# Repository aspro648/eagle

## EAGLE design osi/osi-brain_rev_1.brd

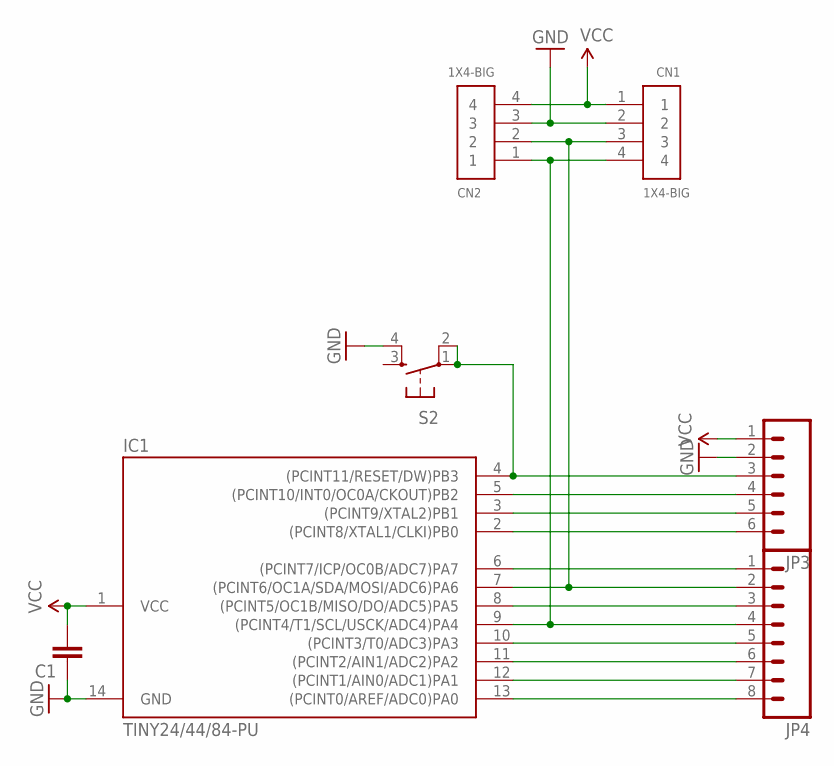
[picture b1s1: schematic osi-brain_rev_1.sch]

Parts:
C1: CAPKIT; CAP-PTH-SMALL-KIT
CN1, CN2: 1X4-BIG; 1X04-BIG
IC1: TINY24/44/84-PU; DIL14
JP3: M06SIP; 1X06
JP4: M081X08; 1X08
S2: TAC_SWITCHPTH; TACTILE-PTH

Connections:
D0: IC1.13 ((PCINT0/AREF/ADC0)PA0), JP4.8
D1: IC1.12 ((PCINT1/AIN0/ADC1)PA1), JP4.7
D2: IC1.11 ((PCINT2/AIN1/ADC2)PA2), JP4.6
D3: IC1.10 ((PCINT3/T0/ADC3)PA3), JP4.5
D4: CN1.4, CN2.1, IC1.9 ((PCINT4/T1/SCL/USCK/ADC4)PA4), JP4.4
D5: IC1.8 ((PCINT5/OC1B/MISO/DO/ADC5)PA5), JP4.3
D6: CN1.3, CN2.2, IC1.7 ((PCINT6/OC1A/SDA/MOSI/ADC6)PA6), JP4.2
D7: IC1.6 ((PCINT7/ICP/OC0B/ADC7)PA7), JP4.1
D8: IC1.5 ((PCINT10/INT0/OC0A/CKOUT)PB2), JP3.4
D9: IC1.3 ((PCINT9/XTAL2)PB1), JP3.5
D10: IC1.2 ((PCINT8/XTAL1/CLKI)PB0), JP3.6
GND: C1.1, CN1.2, CN2.3, IC1.14 (GND), JP3.2, S2.4
RESET: IC1.4 ((PCINT11/RESET/DW)PB3), JP3.3, S2.1, S2.2
VCC: C1.2, CN1.1, CN2.4, IC1.1 (VCC), JP3.1

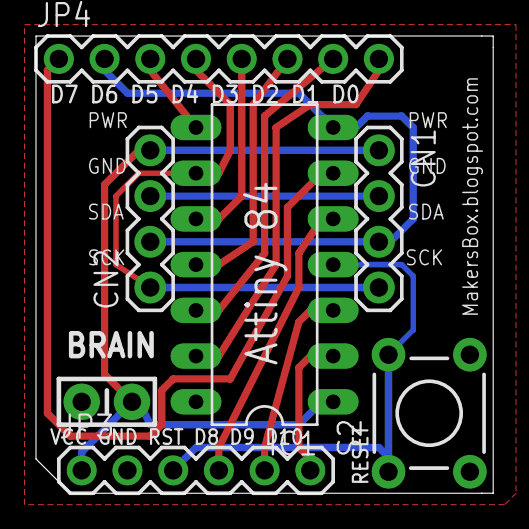
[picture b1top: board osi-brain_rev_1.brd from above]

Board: 2 copper layers, 25.4 x 25.4 mm, 7 parts (0 on the bottom side), 14 nets.

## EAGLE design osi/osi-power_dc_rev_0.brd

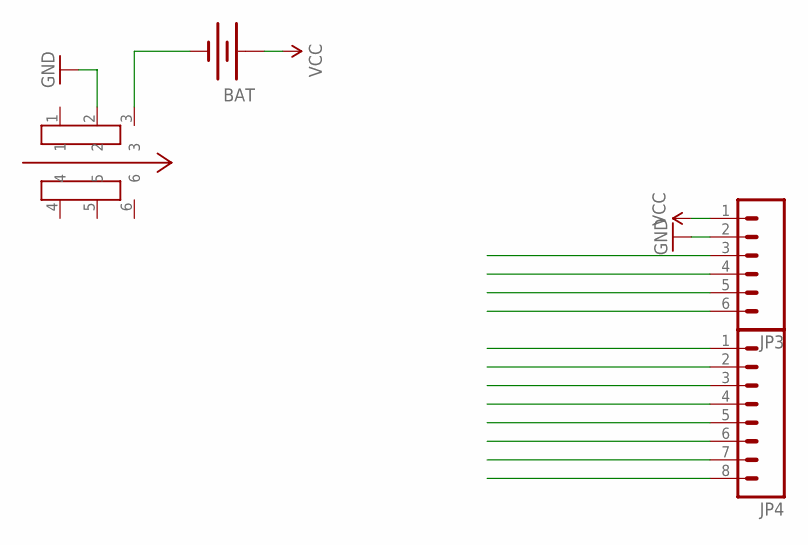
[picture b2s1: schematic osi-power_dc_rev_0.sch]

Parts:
BAT: BATTERY20PTH; BATTCOM_20MM_PTH
JP3: M06SIP; 1X06
JP4: M081X08; 1X08
U$1: SWITCH

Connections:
D0: JP4.8
D1: JP4.7
D2: JP4.6
D3: JP4.5
D4: JP4.4
D5: JP4.3
D6: JP4.2
D7: JP4.1
D8: JP3.4
D9: JP3.5
D10: JP3.6
GND: JP3.2, U$1.2
unnamed: BAT.2 (-), U$1.3
RESET: JP3.3
VCC: BAT.1 (+), JP3.1

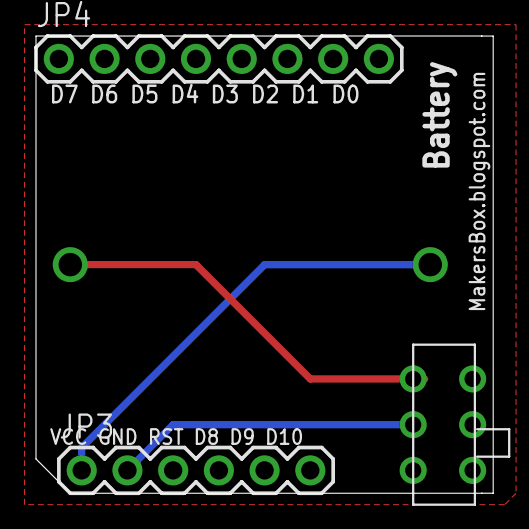
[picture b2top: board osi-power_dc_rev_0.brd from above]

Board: 2 copper layers, 25.4 x 25.4 mm, 4 parts (0 on the bottom side), 3 nets.

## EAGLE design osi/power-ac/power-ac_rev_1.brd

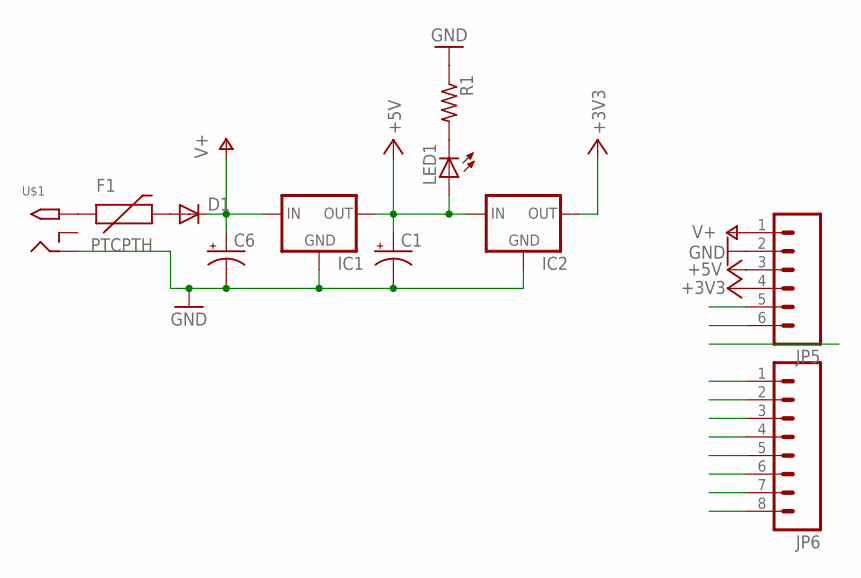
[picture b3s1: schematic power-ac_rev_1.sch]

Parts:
C1, C6: CAP_POLPTH1; CPOL-RADIAL-100UF-25V
D1: DIODE1N4148; DIODE-1N4148
F1: PTCPTH; PTC
IC1: V_REG_78XX-TO-220; TO-220-ALT
IC2: MCP1700INLINE; TO92-INLINE
JP5: M06SIP; 1X06
JP6: M081X08; 1X08
LED1: LED3MM
R1: R-US_0204/2V; 0204V
U$1: 2.1MMJACKTHM; PJ-102A

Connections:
+3V3: IC2.3 (OUT), JP5.4
+5V: C1.1 (+), IC1.OUT, IC2.2 (IN), JP5.3, LED1.A
AREF_D0: JP6.8
D1: JP6.7
D2: JP6.6
D3: JP6.5
D5: JP6.3
D7: JP6.1
D8: JP5.5
D9: JP5.6
GND: C1.2 (-), C6.2 (-), IC1.GND, IC2.1 (GND), JP5.2, R1.1, U$1.RING
unnamed: F1.P$1 (1), U$1.TIP
unnamed: LED1.K (C), R1.2
unnamed: D1.A, F1.P$2 (2)
SCL_D4: JP6.4
SDA_D6: JP6.2
V+: C6.1 (+), D1.C, IC1.IN, JP5.1

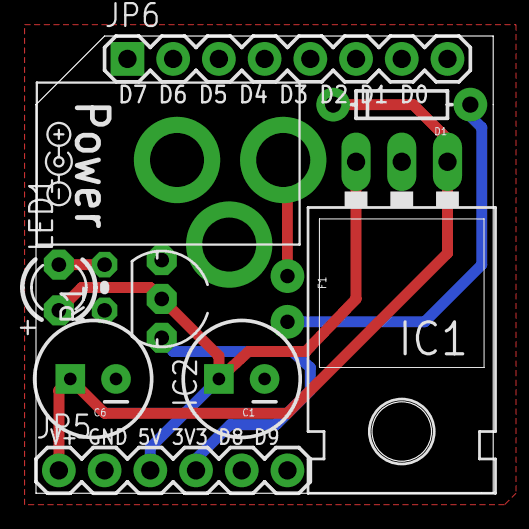
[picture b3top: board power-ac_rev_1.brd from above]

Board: 2 copper layers, 25.4 x 25.4 mm, 13 parts (0 on the bottom side), 7 nets.

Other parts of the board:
U$2: DC_POS_CTR
U$3: DC_POS_CTR-BOTTOM

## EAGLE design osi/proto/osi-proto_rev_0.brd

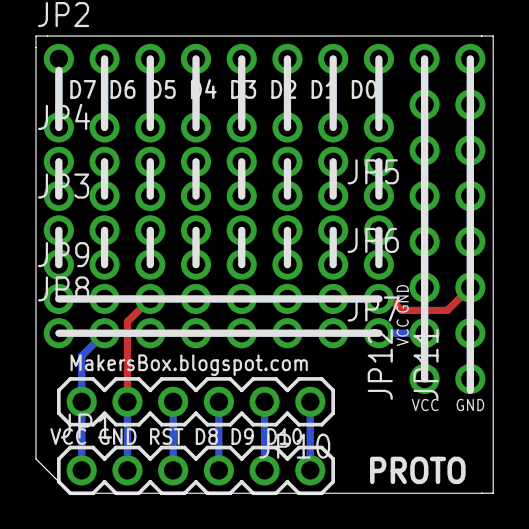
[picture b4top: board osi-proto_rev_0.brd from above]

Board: 2 copper layers, 25.4 x 25.4 mm, 12 parts (0 on the bottom side), 30 nets.

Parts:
JP1, JP10: 1X06
JP2, JP3, JP4, JP5, JP6, JP7, JP8, JP9, JP11, JP12: 1X08

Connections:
D0: JP2.8, JP5.1
D1: JP2.7, JP5.2
D2: JP2.6, JP5.3
D3: JP2.5, JP5.4
D5: JP2.3, JP5.6
D7: JP2.1, JP5.8
GND: JP1.2, JP9.1, JP9.2, JP9.3, JP9.4, JP9.5, JP9.6, JP9.7, JP9.8, JP10.5, JP11.1, JP11.2, JP11.3, JP11.4, JP11.5, JP11.6, JP11.7, JP11.8
unnamed: JP4.8, JP6.1
unnamed: JP4.7, JP6.2
unnamed: JP4.6, JP6.3
unnamed: JP4.5, JP6.4
unnamed: JP4.4, JP6.5
unnamed: JP4.3, JP6.6
unnamed: JP4.2, JP6.7
unnamed: JP4.1, JP6.8
unnamed: JP3.1, JP7.8
unnamed: JP3.2, JP7.7
unnamed: JP3.3, JP7.6
unnamed: JP3.4, JP7.5
unnamed: JP3.5, JP7.4
unnamed: JP3.6, JP7.3
unnamed: JP3.7, JP7.2
unnamed: JP3.8, JP7.1
unnamed: JP1.6, JP10.1
unnamed: JP1.5, JP10.2
unnamed: JP1.4, JP10.3
unnamed: JP1.3, JP10.4
SCK: JP2.2, JP5.7
SDA: JP2.4, JP5.5
VCC: JP1.1, JP8.1, JP8.2, JP8.3, JP8.4, JP8.5, JP8.6, JP8.7, JP8.8, JP10.6, JP12.1, JP12.2, JP12.3, JP12.4, JP12.5, JP12.6, JP12.7, JP12.8

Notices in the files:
parts and their libraries:
SparkFun: Licensing: CC v3.0 Share-Alike You are welcome to use this library for commercial purposes.
